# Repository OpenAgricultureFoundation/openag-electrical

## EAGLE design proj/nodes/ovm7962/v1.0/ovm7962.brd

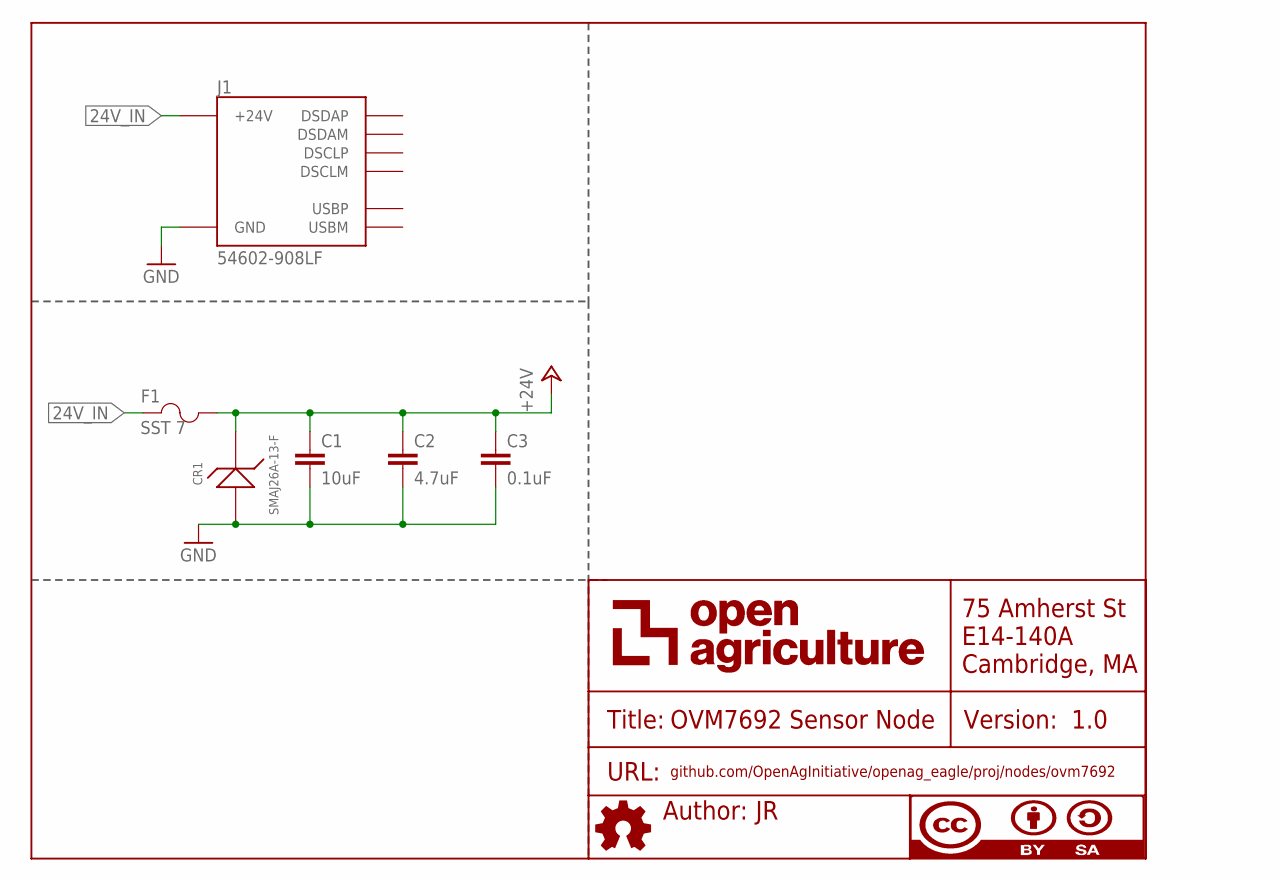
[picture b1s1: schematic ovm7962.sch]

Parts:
C1: 10uF; C0805
C2: 4.7uF; C0805
C3: 0.1uF; C0603
CR1: SMAJ26A-13-F; SMA
F1: SST 7; SS
FRAME1: DOCFIELD
J1: 54602-908LF; OPENAG-V1-RJ45

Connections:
24V_IN: F1.1, J1.24V(6) (+24V)
+24V: C1.1, C2.1, C3.1, CR1.1, F1.2
GND: C1.2, C2.2, C3.2, CR1.2, J1.GND(3) (GND)

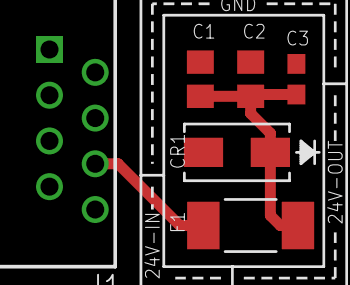
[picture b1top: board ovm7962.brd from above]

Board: 2 copper layers, 8 parts (1 on the bottom side), 3 nets.

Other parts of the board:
U$2: OPENAG-LOGO-750-MIL

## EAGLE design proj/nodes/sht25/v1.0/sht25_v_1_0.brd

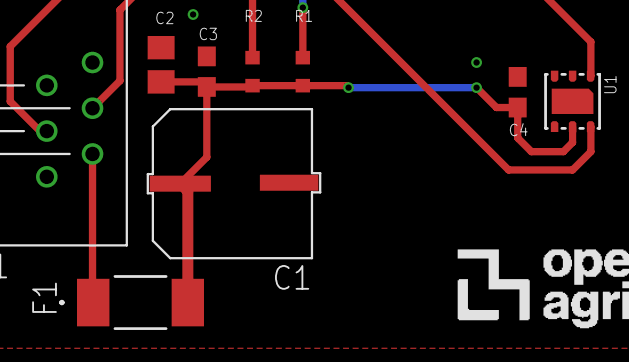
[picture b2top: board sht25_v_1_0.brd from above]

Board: 2 copper layers, 11 parts (1 on the bottom side), 5 nets.

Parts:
C1: 100uF; EEE-1HA101UP
C2: 4.7uF; C0805
C3, C4: 0.1uF; C0603
F1: SST 7; SS
FRAME1: DOCFIELD
J1: RJ12
R1, R2: 1K; RC0603N
U1: SHT25; SHT2X
U$1: OPENAG-LOGO-750-MIL

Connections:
3V3_IN: F1.1, J1.5
+3V3: C1.+, C2.1, C3.1, C4.1, F1.2, R1.2, R2.2, U1.5
GND: C1.-, C2.2, C3.2, C4.2, J1.1, U1.2
SCL: J1.3, R2.1, U1.6
SDA: J1.4, R1.1, U1.1

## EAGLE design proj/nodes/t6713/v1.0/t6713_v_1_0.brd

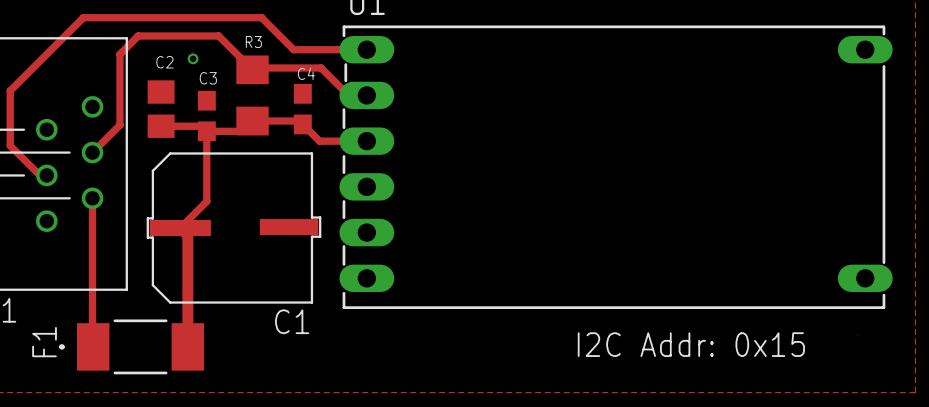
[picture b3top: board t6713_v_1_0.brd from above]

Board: 2 copper layers, 9 parts (1 on the bottom side), 5 nets.

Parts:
C1: 100uF; EEE-1HA101UP
C2: 4.7uF; C0805
C3, C4: 0.1uF; C0603
F1: SST 7; SS
FRAME1: DOCFIELD
J1: RJ12
R3: 4.7K; R1206
U1: T6713-5K; T6713

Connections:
3V3_IN: F1.1, J1.5
+3V3: C1.+, C2.1, C3.1, C4.1, F1.2, R3.1, U1.3
GND: C1.-, C2.2, C3.2, C4.2, J1.1, U1.4, U1.6
SCL: J1.3, R3.2, U1.2
SDA: J1.4, U1.1

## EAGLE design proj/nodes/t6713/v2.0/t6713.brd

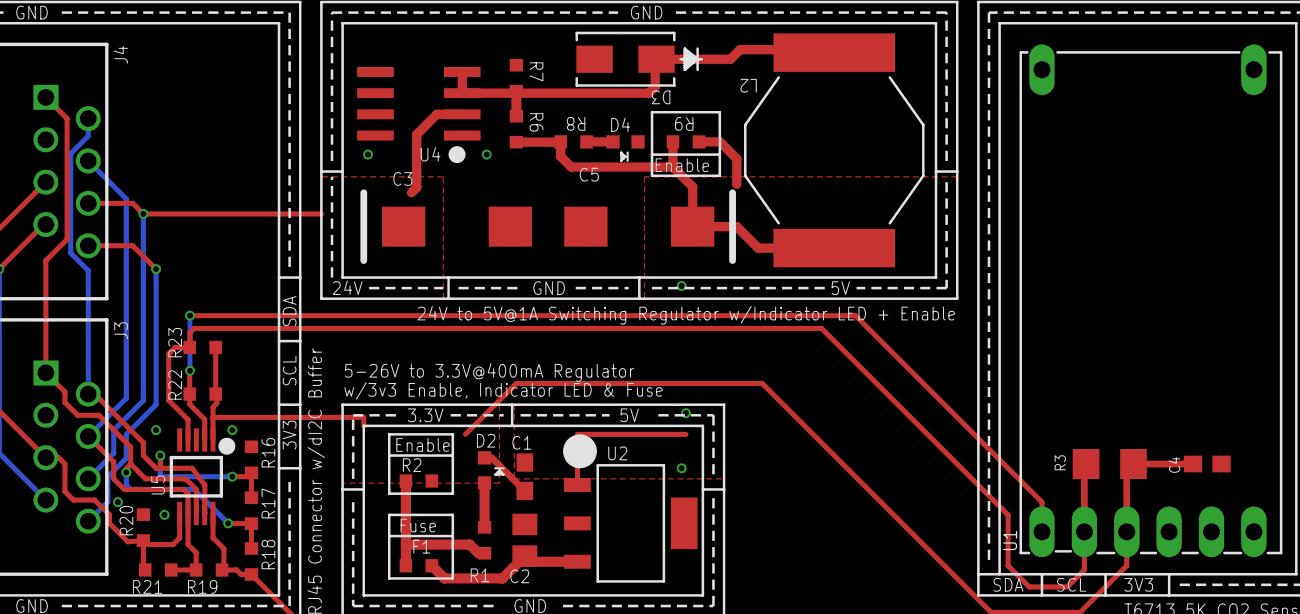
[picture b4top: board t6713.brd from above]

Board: 2 copper layers, 37 parts (1 on the bottom side), 18 nets.

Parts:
C1, C4: 0.1uF; C0603
C2: 10uF; C0805
C3: 15uF; CT7343
C5: 220uF; CT7343
D2, D4: APT1608CGCK; CHIPLED_0603
D3: B260A-13-F; SMA
F1: 0448.400MR; 0603
FRAME1: DOCFIELD
J3, J4: 54602-908LF; OPENAG-V1-RJ45
L2: 68uH; UP2B
R1, R8: 100 OHM; RC0603N
R2, R9: 0 OHM; RC0603N
R3: 4.7K; R1206
R6: 3.01K; RC0603N
R7: 976 Ohm; RC0603N
R16, R17, R18, R19, R20, R21, R22, R23: NV; RC0603N
U1: T6713-5K; T6713
U2: LM2937IMP3.3NOPB; MP04A
U4: MIC4680YM-TR; SOIC8
U5: PCA9615DPJ; SOP50P490X110-10N
U$1, U$2, U$3, U$4: OPENAG-CORNER-MOUNTING-HOLE
U$5: OPENAG-LOGO-750-MIL

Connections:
+3V3: C4.1, R2.2, R3.1, R22.2, R23.2, U1.3, U5.1
+5V: C1.1, R9.2, R18.1, R19.2, U2.1, U5.10
+24V: C3.+, J3.24V(6), J4.24V(6), U4.2
DSCLM: J3.DSCLM(5), J4.DSCLM(5), R20.2, R21.1, U5.6
DSCLP: J3.DSCLP(4), J4.DSCLP(4), R19.1, R21.2, U5.7
DSDAM: J3.DSDAM(2), J4.DSDAM(2), R16.1, R17.2, U5.9
DSDAP: J3.DSDAP(1), J4.DSDAP(1), R17.1, R18.2, U5.8
GND: C1.2, C2.2, C3.-, C4.2, C5.-, D2.C, D3.2, D4.C, J3.GND(3), J4.GND(3), R7.1, R16.2, R20.1, U1.4, U1.6, U2.2, U4.1, U4.5, U4.6, U4.7, U4.8, U5.5
unnamed: D3.1, L2.1, R6.1, R7.2, U4.3, U4.4
unnamed: D2.A, R1.1
unnamed: C2.1, F1.1, U2.3
unnamed: D4.A, R8.1
unnamed: C5.+, L2.2, R6.2, R8.2, R9.1
REG_3V3_400MA: F1.2, R1.2, R2.1
SCL: R3.2, R23.1, U1.2, U5.4
SDA: R22.1, U1.1, U5.2
USBM: J3.USBM(8), J4.USBM(8)
USBP: J3.USBP(7), J4.USBP(7)

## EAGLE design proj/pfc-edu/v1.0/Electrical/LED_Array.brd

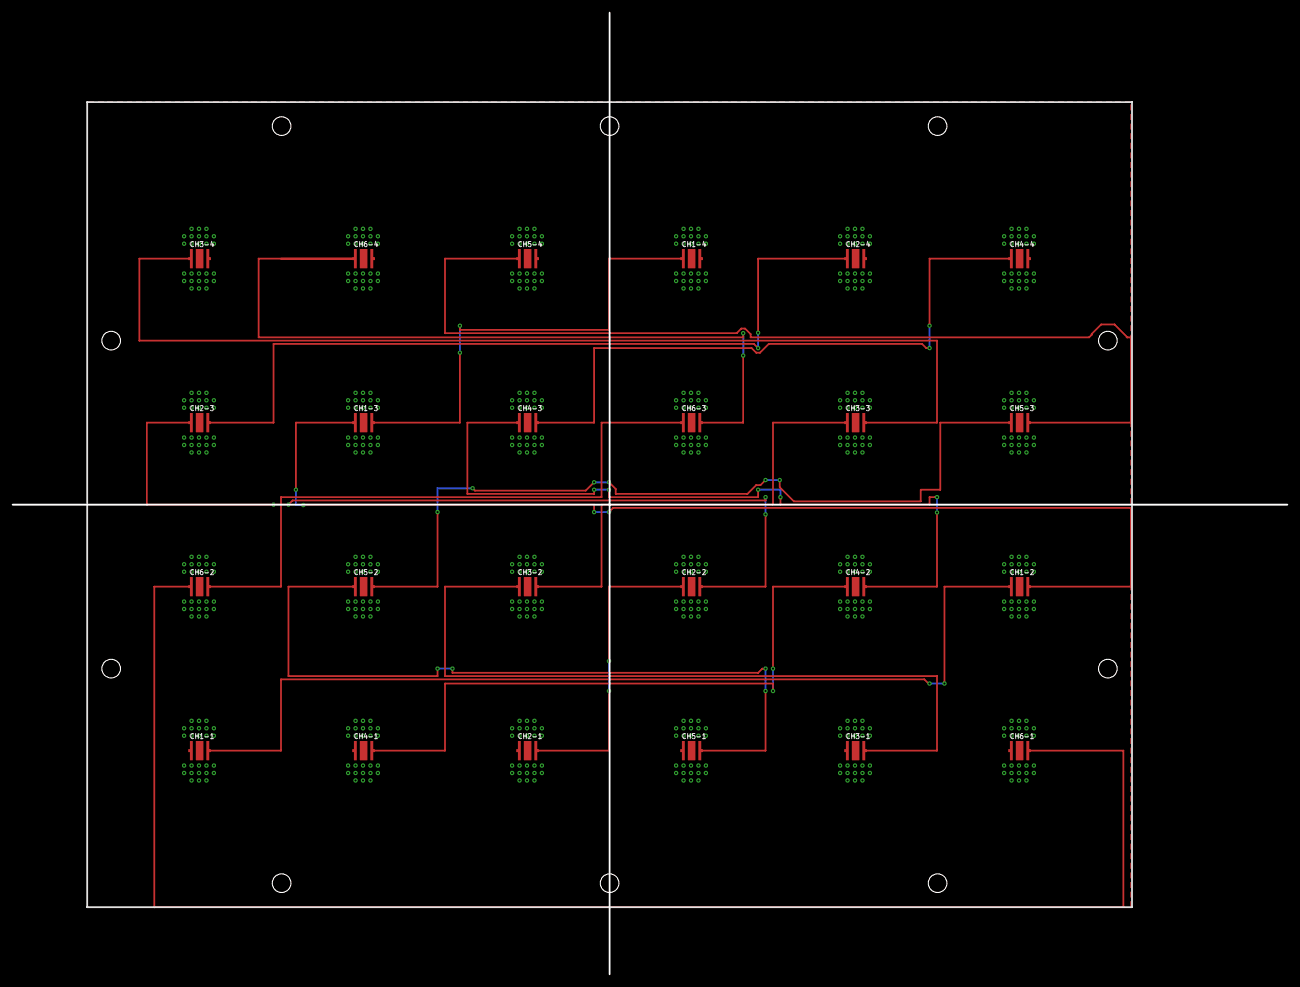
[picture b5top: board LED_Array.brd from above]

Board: 2 copper layers, 217.2 x 163.8 mm, 24 parts (0 on the bottom side), 19 nets.

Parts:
CH1-1, CH1-2, CH1-3, CH1-4, CH2-1, CH2-2, CH2-3, CH2-4, CH3-1, CH3-2, CH3-3, CH3-4, CH4-1, CH4-2, CH4-3, CH4-4, CH5-1, CH5-2, CH5-3, CH5-4, CH6-1, CH6-2, CH6-3, CH6-4: XP-E; CREE-XLAMP-XP-E

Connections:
unnamed: CH2-1.A, CH2-1.A@1, CH2-2.C, CH2-2.C@1
unnamed: CH2-2.A, CH2-2.A@1, CH2-3.C, CH2-3.C@1
unnamed: CH2-3.A, CH2-3.A@1, CH2-4.C, CH2-4.C@1
unnamed: CH4-1.A, CH4-1.A@1, CH4-2.C, CH4-2.C@1
unnamed: CH4-2.A, CH4-2.A@1, CH4-3.C, CH4-3.C@1
unnamed: CH4-3.A, CH4-3.A@1, CH4-4.C, CH4-4.C@1
unnamed: CH6-1.A, CH6-1.A@1, CH6-2.C, CH6-2.C@1
unnamed: CH6-2.A, CH6-2.A@1, CH6-3.C, CH6-3.C@1
unnamed: CH6-3.A, CH6-3.A@1, CH6-4.C, CH6-4.C@1
unnamed: CH1-1.A, CH1-1.A@1, CH1-2.C, CH1-2.C@1
unnamed: CH1-2.A, CH1-2.A@1, CH1-3.C, CH1-3.C@1
unnamed: CH1-3.A, CH1-3.A@1, CH1-4.C, CH1-4.C@1
unnamed: CH3-1.A, CH3-1.A@1, CH3-2.C, CH3-2.C@1
unnamed: CH3-2.A, CH3-2.A@1, CH3-3.C, CH3-3.C@1
unnamed: CH3-3.A, CH3-3.A@1, CH3-4.C, CH3-4.C@1
unnamed: CH5-1.A, CH5-1.A@1, CH5-2.C, CH5-2.C@1
unnamed: CH5-2.A, CH5-2.A@1, CH5-3.C, CH5-3.C@1
unnamed: CH5-3.A, CH5-3.A@1, CH5-4.C, CH5-4.C@1
T: CH1-1.THERM, CH1-2.THERM, CH1-3.THERM, CH1-4.THERM, CH2-1.THERM, CH2-2.THERM, CH2-3.THERM, CH2-4.THERM, CH3-1.THERM, CH3-2.THERM, CH3-3.THERM, CH3-4.THERM, CH4-1.THERM, CH4-2.THERM, CH4-3.THERM, CH4-4.THERM, CH5-1.THERM, CH5-2.THERM, CH5-3.THERM, CH5-4.THERM, CH6-1.THERM, CH6-2.THERM, CH6-3.THERM, CH6-4.THERM

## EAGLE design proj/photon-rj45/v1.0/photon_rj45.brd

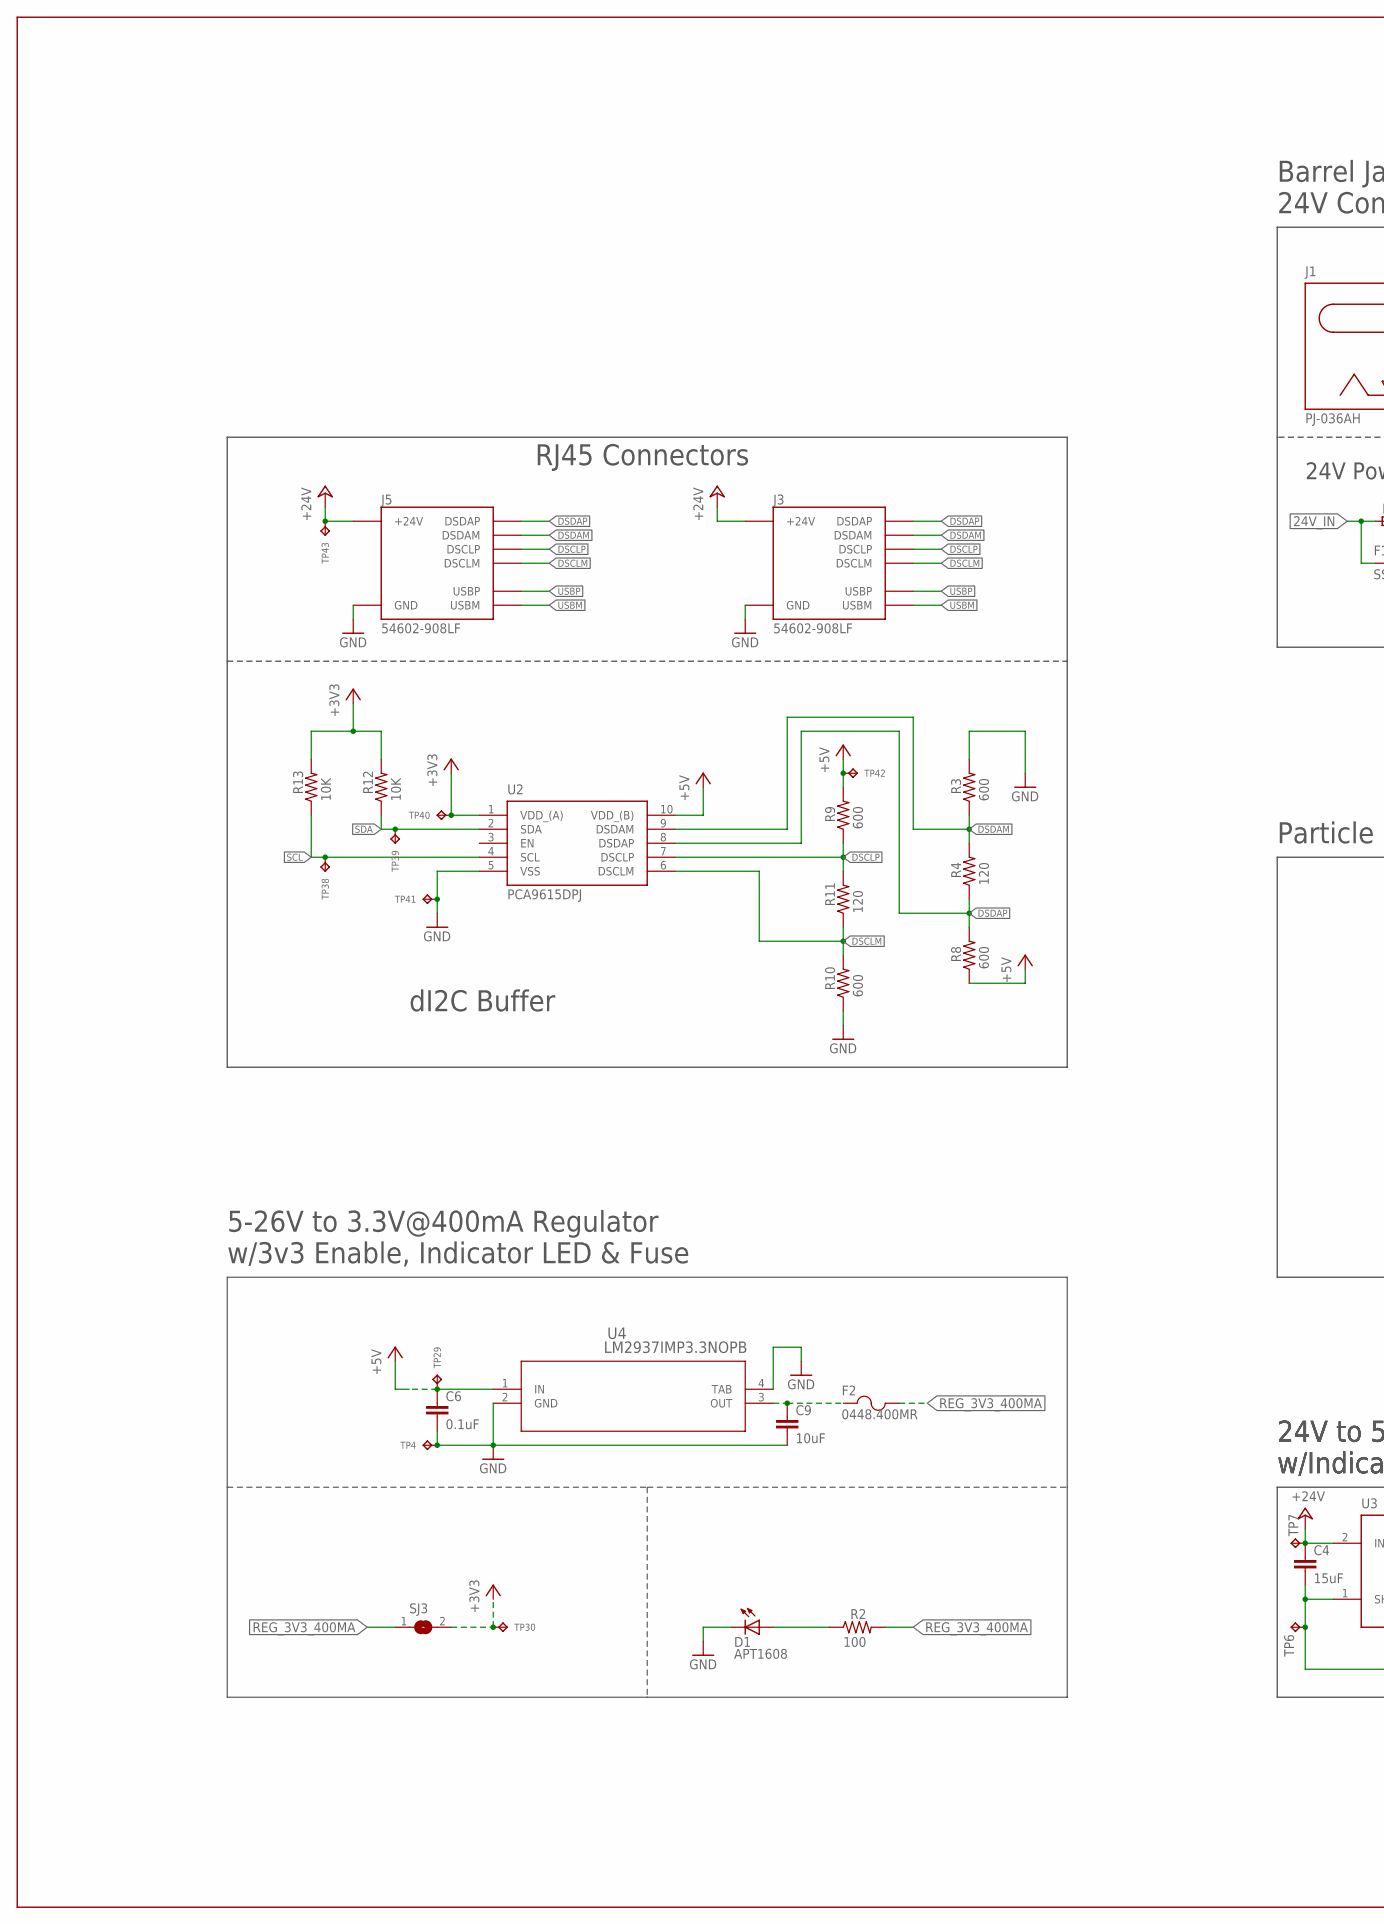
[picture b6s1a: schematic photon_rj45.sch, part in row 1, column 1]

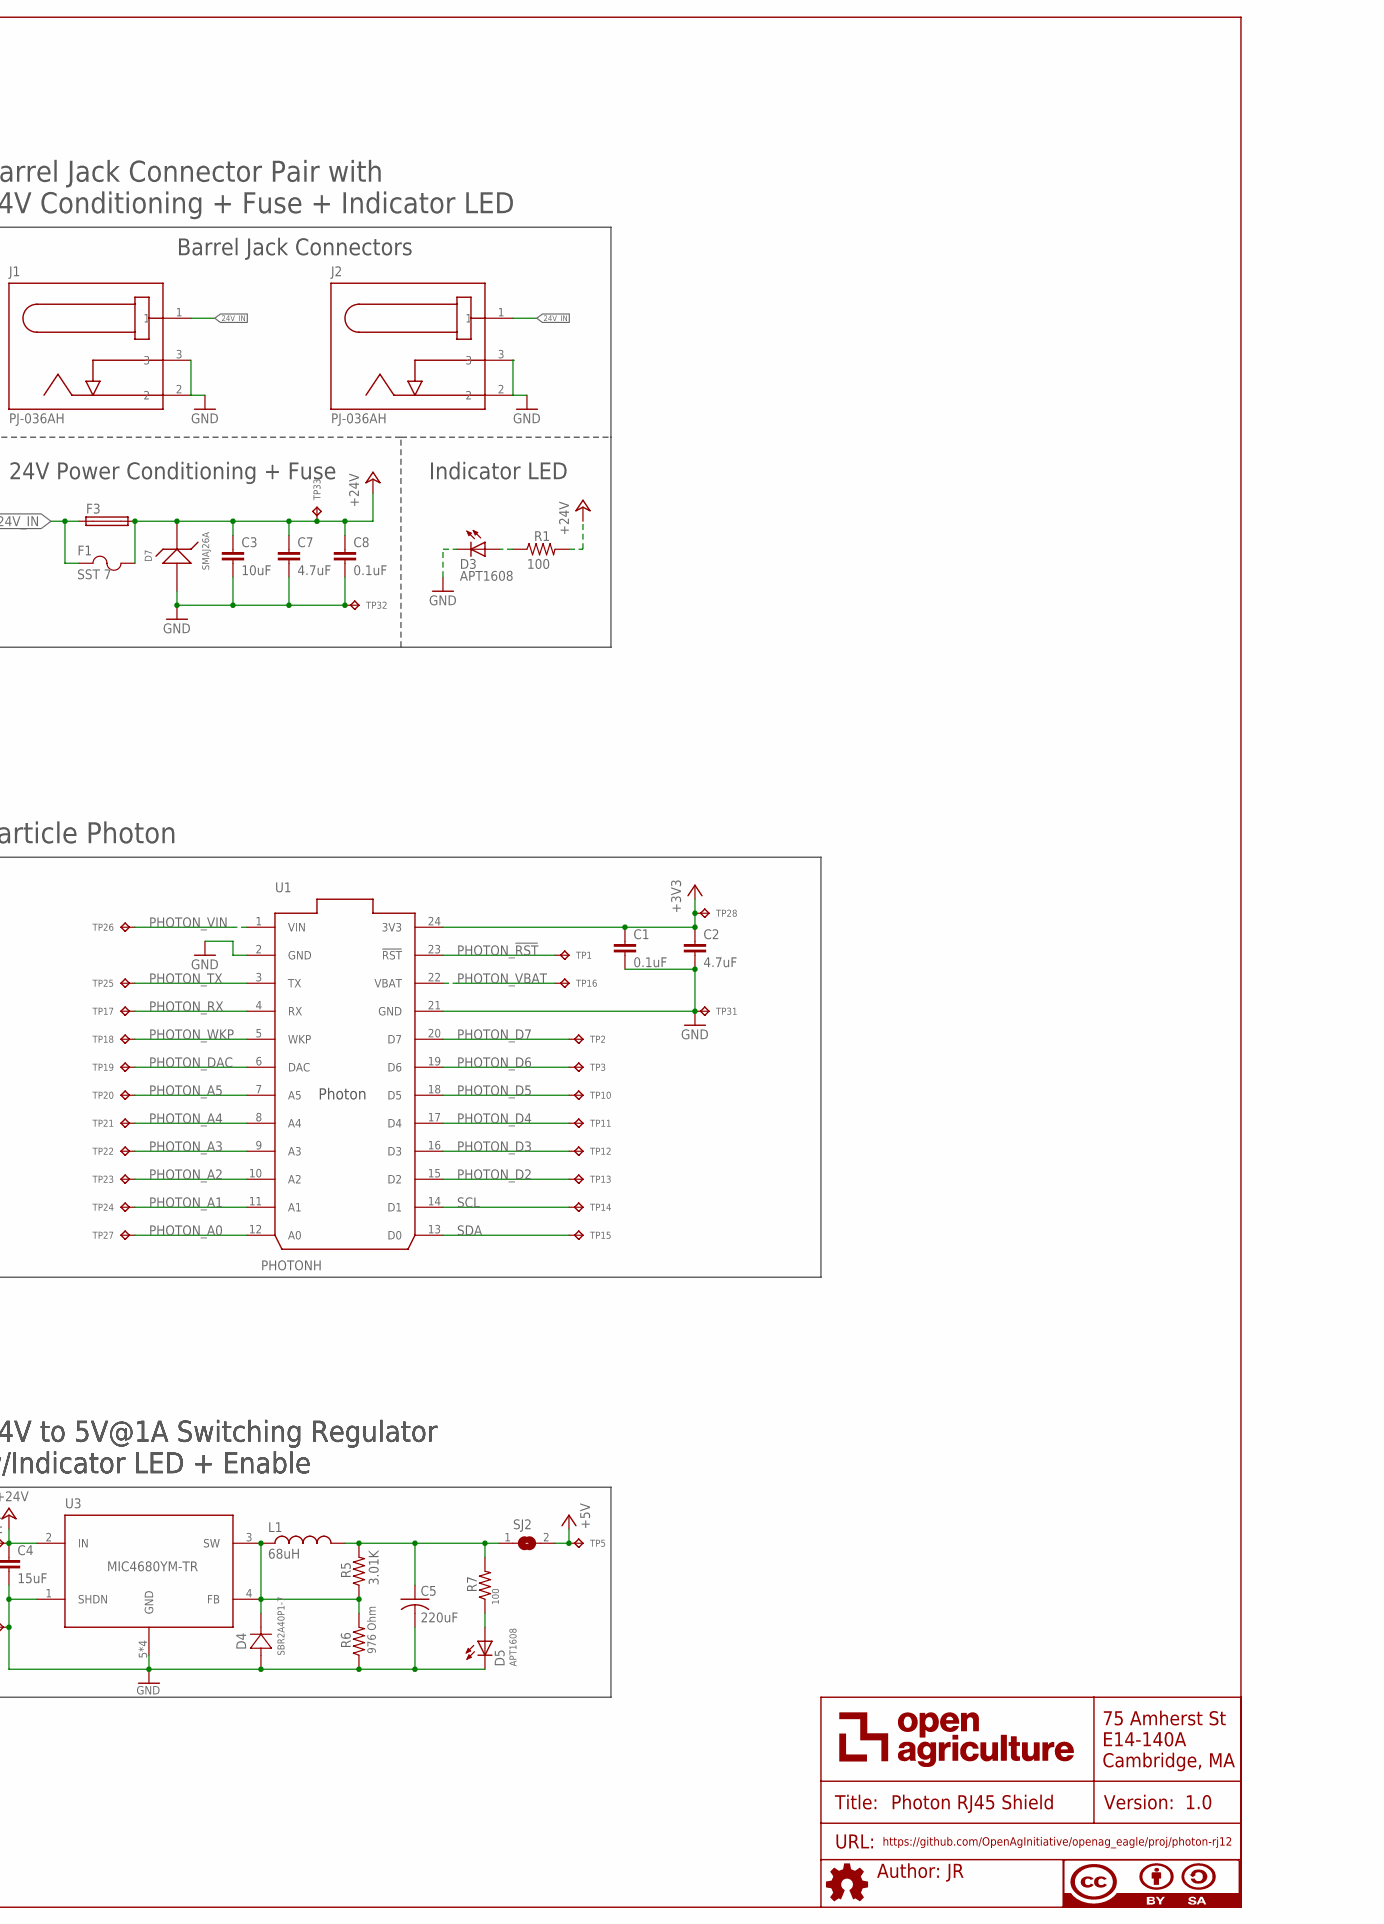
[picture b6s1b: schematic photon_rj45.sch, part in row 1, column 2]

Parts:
C1, C6, C8: 0.1uF; C0603
C2, C7: 4.7uF; C0805
C3, C9: 10uF; C0805
C4: 15uF; C0805
C5: 220uF; CT7343
D1, D3, D5: APT1608; CHIPLED_0603
D4: SBR2A40P1-7; POWERDI123
D7: SMAJ26A; SMA
F1: SST 7; SS
F2: 0448.400MR; 0603
F3: GSH15
FRAME1: DOCFIELD
J1, J2: PJ-036AH
J3, J5: 54602-908LF; OPENAG-V1-RJ45
L1: 68uH; UP2B
R1, R2, R7: 100; RC0603N
R3, R8, R9, R10: 600; RC0603N
R4, R11: 120; RC0603N
R5: 3.01K; RC0603N
R6: 976 Ohm; RC0603N
R12, R13: 10K; RC0603N
SJ2, SJ3: SOLDERJUMPERREFLOW_NOPASTE; SOLDERJUMPER_REFLOW_NOPASTE
TP1, TP2, TP3, TP10, TP11, TP12, TP13, TP14, TP15, TP16, TP17, TP18, TP19, TP20, TP21, TP22, TP23, TP24, TP25, TP26, TP27, TP28, TP31: TPTP04R; TP04R
TP4, TP5, TP6, TP7, TP29, TP30, TP32, TP33, TP38, TP39, TP40, TP41, TP42, TP43: TPTP06R; TP06R
U1: PHOTONH; PHOTON
U2: PCA9615DPJ; SOP50P490X110-10N
U3: MIC4680YM-TR; SOIC8
U4: LM2937IMP3.3NOPB; MP04A

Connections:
24V_IN: F1.1, F3.1, J1.1, J2.1
+3V3: C1.1, C2.1, R12.2, R13.2, SJ3.2, TP28.1, TP30.TP, TP40.TP, U1.24 (3V3), U2.1 (VDD_(A))
+5V: C6.1, R8.1, R9.2, SJ2.2, TP5.TP, TP29.TP, TP42.TP, U2.10 (VDD_(B)), U4.1 (IN)
+24V: C3.1, C4.1, C7.1, C8.1, D7.1, F1.2, F3.2, J3.24V(6) (+24V), J5.24V(6) (+24V), R1.2, TP7.TP, TP33.TP, TP43.TP, U3.2 (IN)
DSCLM: J3.DSCLM(5) (DSCLM), J5.DSCLM(5) (DSCLM), R10.2, R11.1, U2.6 (DSCLM)
DSCLP: J3.DSCLP(4) (DSCLP), J5.DSCLP(4) (DSCLP), R9.1, R11.2, U2.7 (DSCLP)
DSDAM: J3.DSDAM(2) (DSDAM), J5.DSDAM(2) (DSDAM), R3.1, R4.2, U2.9 (DSDAM)
DSDAP: J3.DSDAP(1) (DSDAP), J5.DSDAP(1) (DSDAP), R4.1, R8.2, U2.8 (DSDAP)
GND: C1.2, C2.2, C3.2, C4.2, C5.- (2(-)), C6.2, C7.2, C8.2, C9.2, D1.C, D3.C, D4.- (21), D5.C, D7.2, J1.2, J1.3, J2.2, J2.3, J3.GND(3) (GND), J5.GND(3) (GND), R3.2, R6.1, R10.1, TP4.TP, TP6.TP, TP31.1, TP32.TP, TP41.TP, U1.2 (GND), U1.21 (GND), U2.5 (VSS), U3.1 (SHDN), U3.5 (GND), U3.6 (GND), U3.7 (GND), U3.8 (GND), U4.2 (GND), U4.4 (TAB)
unnamed: D1.A, R2.1
unnamed: C9.1, F2.1, U4.3 (OUT)
unnamed: D3.A, R1.1
unnamed: D4.+ (12), L1.1, R5.1, R6.2, U3.3 (SW), U3.4 (FB)
unnamed: D5.A, R7.1
unnamed: C5.+ (1(+)), L1.2, R5.2, R7.2, SJ2.1
PHOTON_!RST!: TP1.1, U1.23 (!RST)
PHOTON_A0: TP27.1, U1.12 (A0)
PHOTON_A1: TP24.1, U1.11 (A1)
PHOTON_A2: TP23.1, U1.10 (A2)
PHOTON_A3: TP22.1, U1.9 (A3)
PHOTON_A4: TP21.1, U1.8 (A4)
PHOTON_A5: TP20.1, U1.7 (A5)
PHOTON_D2: TP13.1, U1.15 (D2)
PHOTON_D3: TP12.1, U1.16 (D3)
PHOTON_D4: TP11.1, U1.17 (D4)
PHOTON_D5: TP10.1, U1.18 (D5)
PHOTON_D6: TP3.1, U1.19 (D6)
PHOTON_D7: TP2.1, U1.20 (D7)
PHOTON_DAC: TP19.1, U1.6 (DAC)
PHOTON_RX: TP17.1, U1.4 (RX)
PHOTON_TX: TP25.1, U1.3 (TX)
PHOTON_VBAT: TP16.1, U1.22 (VBAT)
PHOTON_VIN: TP26.1, U1.1 (VIN)
PHOTON_WKP: TP18.1, U1.5 (WKP)
REG_3V3_400MA: F2.2, R2.2, SJ3.1
SCL: R13.1, TP14.1, TP38.TP, U1.14 (D1), U2.4 (SCL)
SDA: R12.1, TP15.1, TP39.TP, U1.13 (D0), U2.2 (SDA)
USBM: J3.USBM(8) (USBM), J5.USBM(8) (USBM)
USBP: J3.USBP(7) (USBP), J5.USBP(7) (USBP)

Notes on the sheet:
5-26V to 3.3V@400mA Regulator w/3v3 Enable, Indicator LED & Fuse
24V to 5V@1A Switching Regulator w/Indicator LED + Enable
Particle Photon
Barrel Jack Connectors
Barrel Jack Connector Pair with 24V Conditioning + Fuse + Indicator LED
24V Power Conditioning + Fuse
Indicator LED
dI2C Buffer
RJ45 Connectors

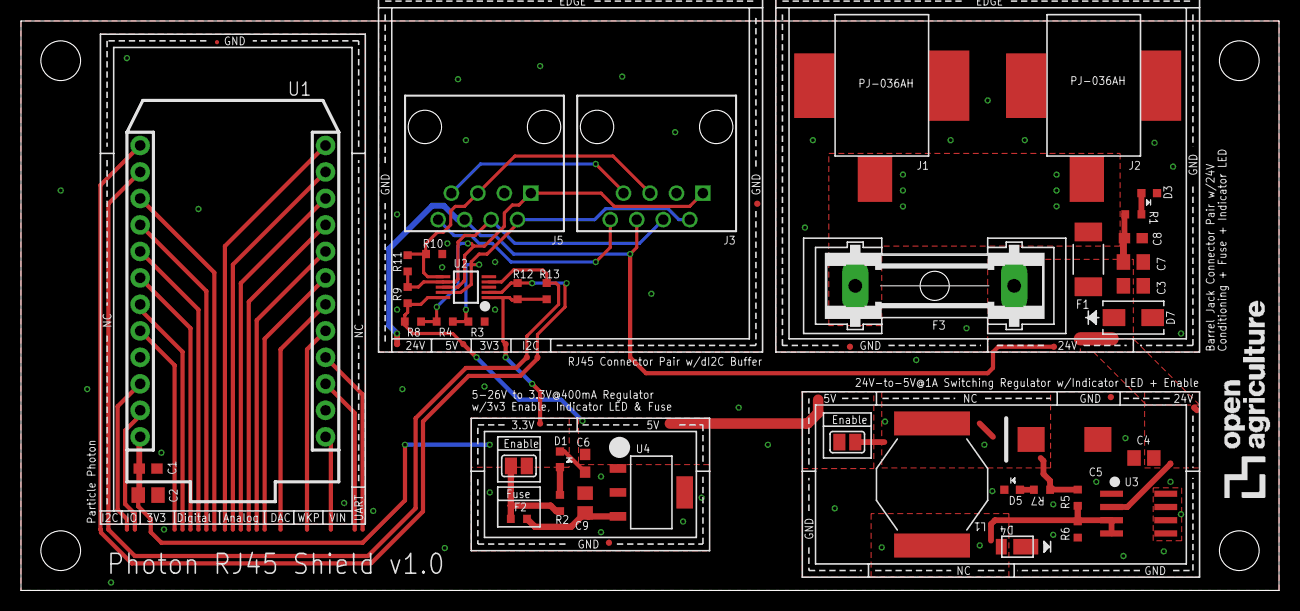
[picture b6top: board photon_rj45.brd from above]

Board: 2 copper layers, 120.7 x 54.6 mm, 84 parts (1 on the bottom side), 39 nets.

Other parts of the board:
U$1, U$2, U$3, U$4: OPENAG-CORNER-MOUNTING-HOLE
U$5: OPENAG-LOGO-750-MIL
